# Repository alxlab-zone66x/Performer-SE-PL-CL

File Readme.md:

# Micromac Performer SE/Plus/Classic Clone

This is a recreation of the MicroMac SE/Plus/Classic accelerator.  
The schematics have been reverse engineered and a new PCB was created based on the schematics.

The provided PCB files are licensed under CC-BY-NC-SA - they are NOT intended for commercial use.  

## Notes on GALs and jumpers

The original GALs have been dumped. GAL16V8-15 as well as PALCE16V8-15 have been tested as suitable replacement.
Faster/slower chips as well as ATF16V8 of any speed haven't been tested so far.

U3, U4, U5 and U6 are mandatory. U7 is only needed for operation in Macintosh Plus and Classic.
Close SJ2 if U7 isn't installed. SJ2 HAS to be open when U7 is installed.

Close SJ1 to run the optional 68882 off the 16MHz accelerator clock.
Install an oscillator and open SJ1 to run the 68882 at any speed.
The original design used 25MHz which has been verified to work on the clone as well.

I have not found a socket that allows secure installation over the PLCC CPU in the Macintosh Classic.
Proper operation has been tested in the Macintosh Plus and SE but so far not on the Classic.

## Board Files

The provided gerber files have been generated using the JLCPCB EAGLE cam job files.  

The Kicad project files are placed inside the `kicad` folder. It's been slightly tweaked from the original Eagle project to pass DRC. The silkscreen for the Macintosh Classic and Macintosh Plus were moved to the bottom.

| Board Revision                | Description                                                  |                                                              |
| :---------------------------- | ------------------------------------------------------------ | ------------------------------------------------------------ |
| Performer PL-CL-SE            | Original recreation by Bolle.                                | [gerbers and bom](production/Performer_PL-CL-SE.zip)         |
| Performer SE v1.0 socket pga  | SE only, 2 layers, PGA FPU, PGA CPU, PLCC-20 through-hole sockets | [gerbers and assembly](production/Performer-SE_v1.0_socket-pga.zip) |
| Performer SE v1.1 socket pga  | SE only, 2 layers, PGA FPU, PGA CPU, PLCC-20 through-hole sockets | [gerbers and assembly](production/Performer-SE_v1.1_socket-pga.zip) |
| Performer SE v1.0 socket plcc | SE only, 2 layers, PLCC FPU, PGA CPU, PLCC-20 through-hole sockets | [gerbers and assembly](production/Performer-SE_v1.0_socket-plcc.zip) |
| Performer SE v1.1 socket plcc | SE only, 2 layers, PLCC FPU, PGA CPU, PLCC-20 through-hole sockets | [gerbers and assembly](production/Performer-SE_v1.1_socket-plcc.zip) |

## Bill of Materials

### Performer SE

Parts shared between the Performer SE design variations.

| Quantity | Description                                     | Designators                                                  | Product Number                                               |
| :------- | ----------------------------------------------- | ------------------------------------------------------------ | ------------------------------------------------------------ |
| 4        | 100uF 6.3v 1206 mlcc                            | C1, C2, C3, C4                                               |                                                              |
| 5        | 0.1uF 6.3v 1206 mlcc                            | C5, C6, C7, C8, C9                                           |                                                              |
| 18       | 4.7kOhms 1/4W 1206 resistor                     | R1, R2, R3, R4, R5, R6, R7, R8, R9, R10, R11, R12, R13, R14, R15, R16, R17, R18 |                                                              |
| 4-6      | 0.5mm press-fit pin socket (optional)           | QG1                                                          | [0531-0-15-15-31-27-10-0](docs/datasheets/Mill-Max_0531-0-15-15-31-27-10-0.pdf) |
| 1        | 25MHz oscillator 8-pin or 14-pin dip (optional) | QG1                                                          | [ECS-2200B-250](docs/datasheets/ECS_ECS-2200B-250.pdf), [ECS-100AX-250](docs/datasheets/ECS_ECS-100AX-250.pdf) |
| 1        | pga-128 through-hole socket (optional)          | U1                                                           |                                                              |
| 4        | plcc-20 through-hole socket                     | U3, U4, U5, U6                                               | [PLCC-20-AT](docs/datasheets/Adam-Tech_PLCC-20-AT.pdf)       |

### Performer SE - PLCC FPU

| Quantity | Description                 | Designators | Product Number                                         |
| :------- | --------------------------- | ----------- | ------------------------------------------------------ |
| 1        | plcc-68 through-hole socket | U2          | [PLCC-68-AT](docs/datasheets/Adam-Tech_PLCC-68-AT.pdf) |

### Performer SE - PGA FPU

| Quantity | Description                           | Designators | Product Number |
| :------- | ------------------------------------- | ----------- | -------------- |
| 1        | pga-68 through-hole socket (optional) | U2          |                |

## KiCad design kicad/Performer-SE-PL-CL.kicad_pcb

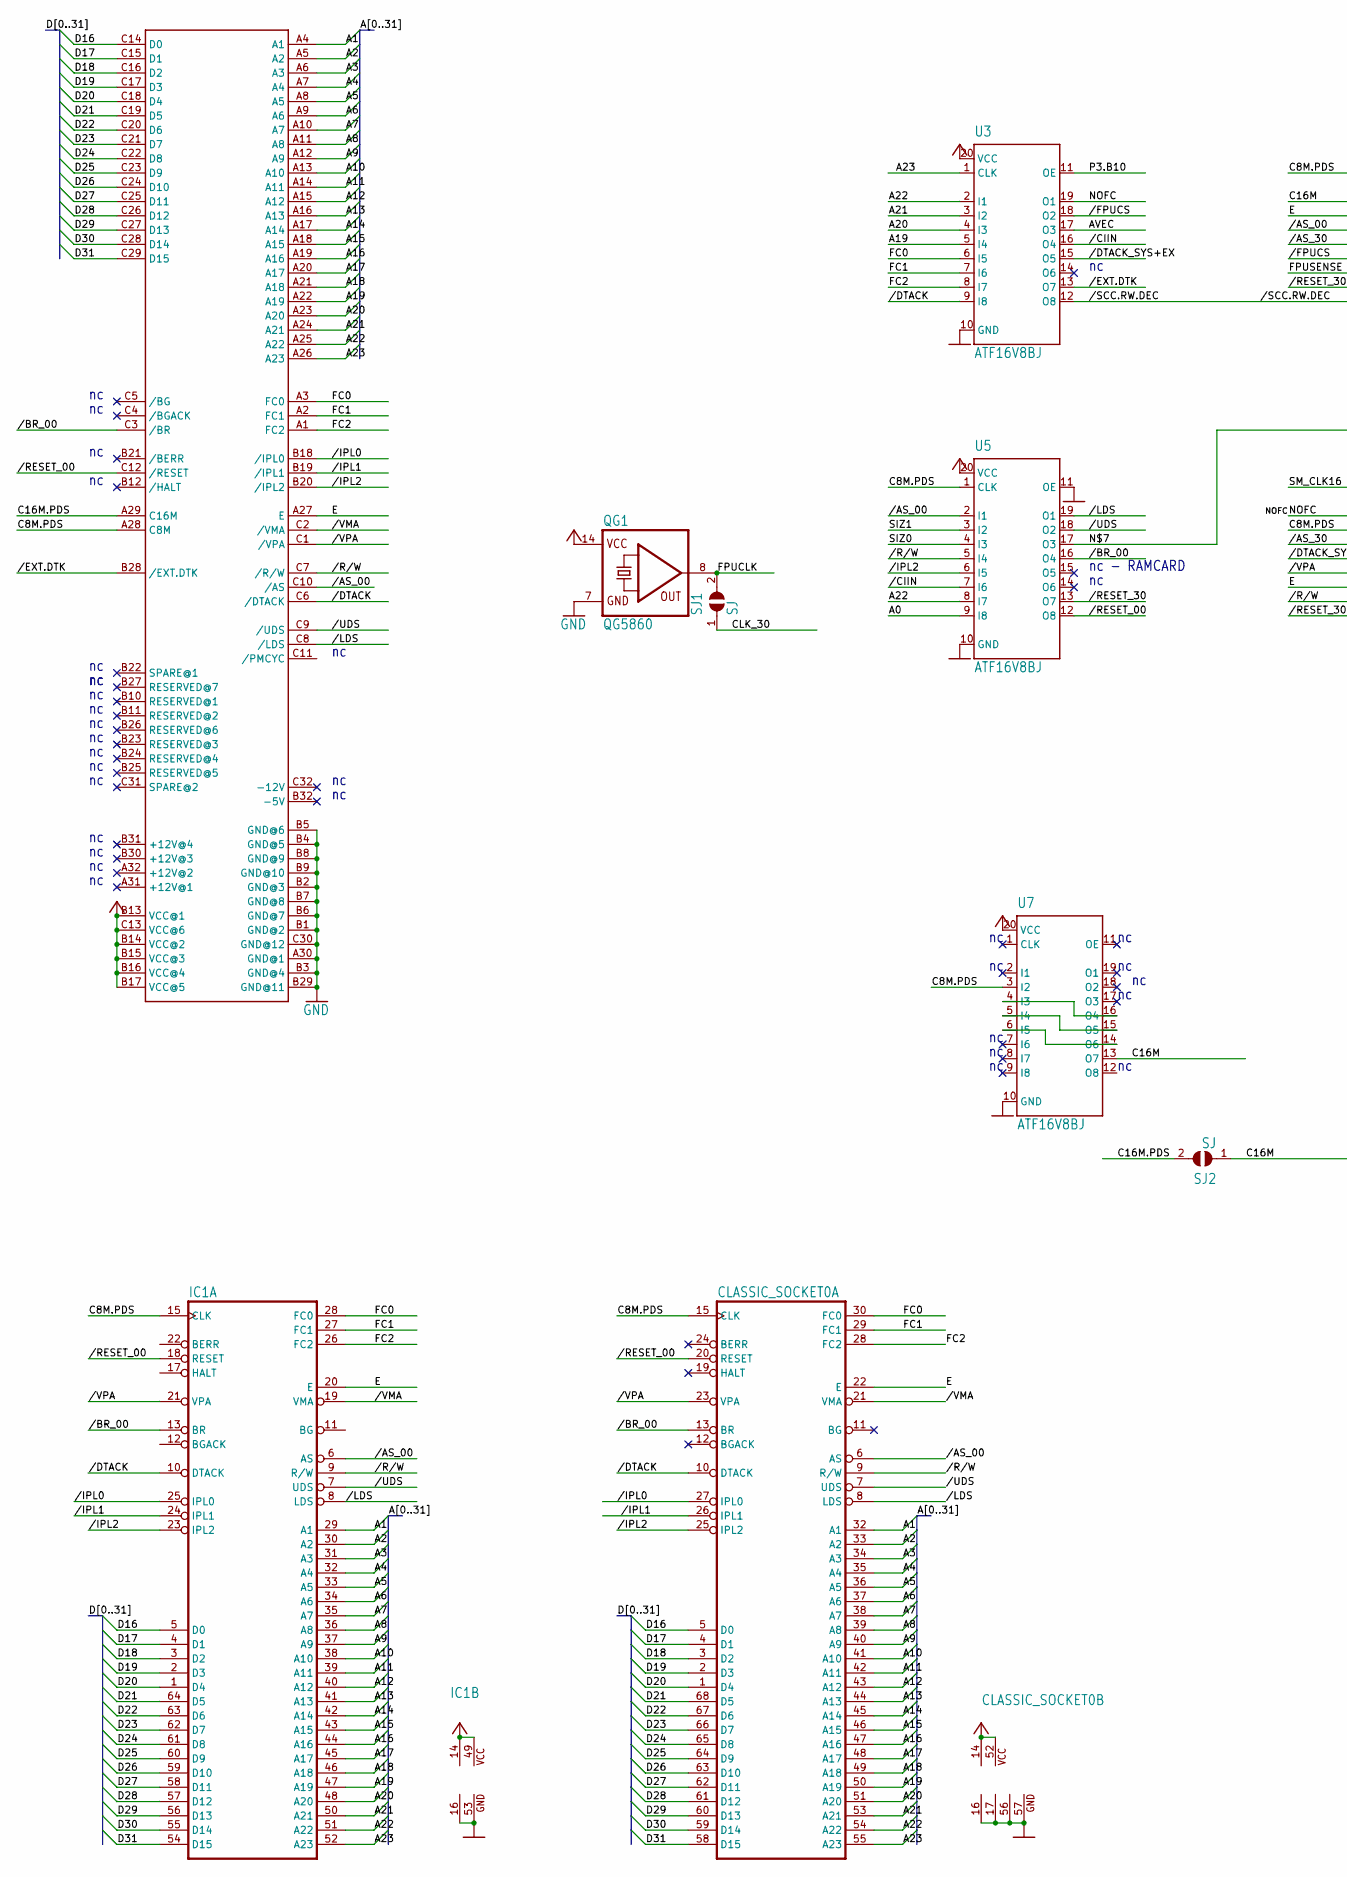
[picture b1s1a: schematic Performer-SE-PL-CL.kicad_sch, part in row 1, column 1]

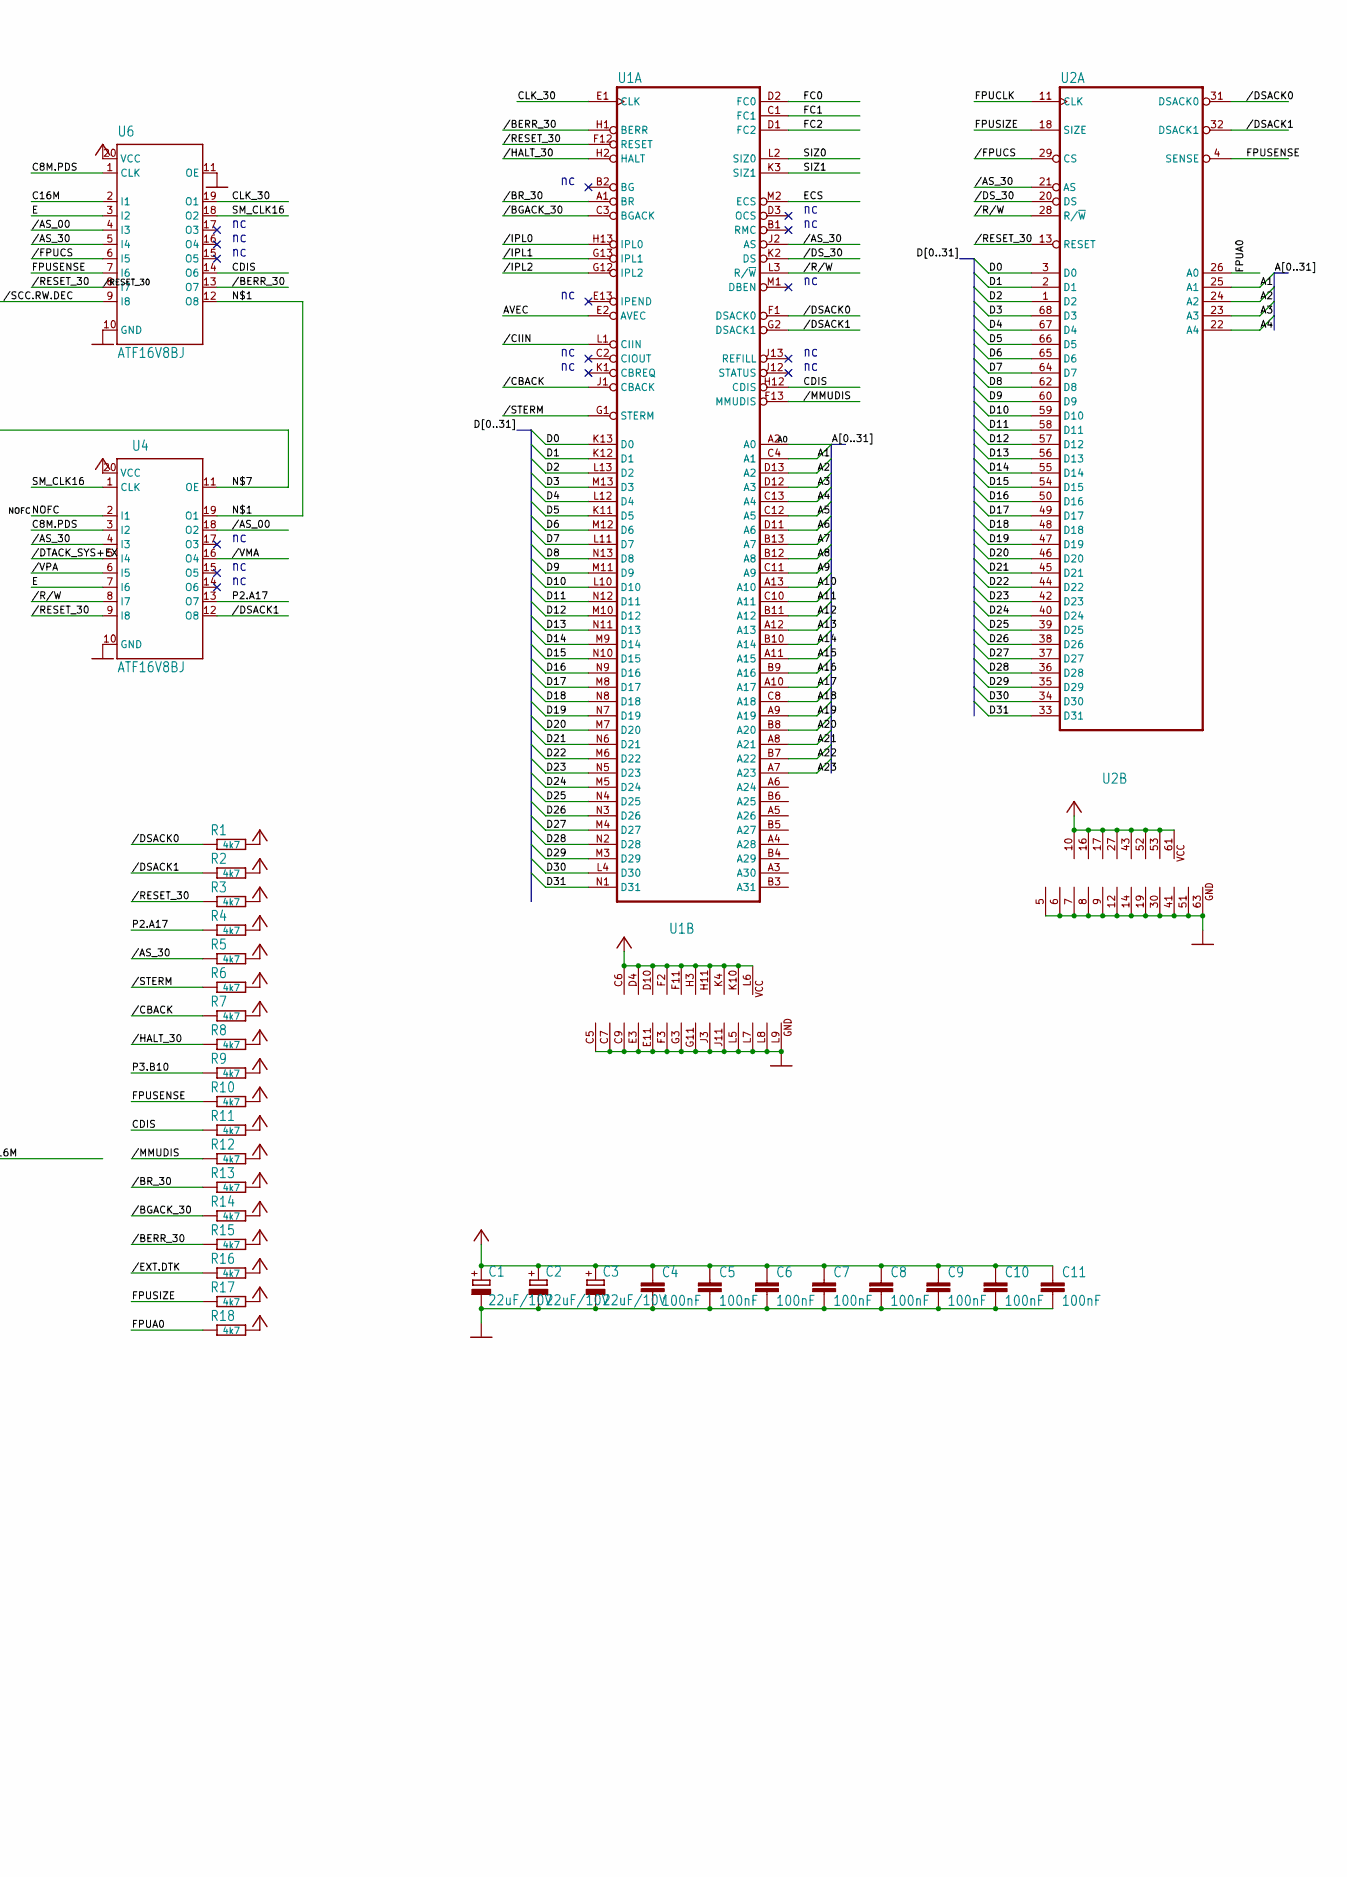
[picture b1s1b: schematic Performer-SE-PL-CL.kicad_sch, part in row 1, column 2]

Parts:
C1, C2, C3: 22uF/10V; CP_EIA-6032-15_Kemet-U_Pad2.25x2.35mm_HandSolder
C4, C5, C6, C7, C8, C9, C10, C11: 100nF; C_1206_3216Metric_Pad1.60x1.80mm_HandSolder
CLASSIC_SOCKET0: MC68000FN-SOC; PLCC-68_THT-Socket_Mirror
IC1: MC68000P; DIP-64_W22.86mm_LongPads_Mirror
J1: MAC_SE_PDS; DIN41612_R_3x32_Male_Vertical_THT_Mirror_NoMountingHoles
QG1: QG5860; Oscillator_DIP-14
R1, R2, R3, R4, R5, R6, R7, R8, R9, R10, R11, R12, R13, R14, R15, R16, R17, R18: 4k7; R_1206_3216Metric_Pad1.60x1.80mm_HandSolder
SJ1, SJ2: SJ; SolderJumper-2_P1.3mm_Open_TrianglePad1.0x1.5mm
U1: MC68030RC; CPGA-128_Layout13x13_MC68030
U2: MC68881FN-SOC; PLCC-68_THT-Socket
U3, U4, U5, U6, U7: ATF16V8BJ; PLCC-20

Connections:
/A0: U1.A2 (A0), U5.9 (I8)
/A1: CLASSIC_SOCKET0.32 (A1), IC1.29 (A1), J1.A4 (A1), U1.C4 (A1), U2.25 (A1)
/A2: CLASSIC_SOCKET0.33 (A2), IC1.30 (A2), J1.A5 (A2), U1.D13 (A2), U2.24 (A2)
/A3: CLASSIC_SOCKET0.34 (A3), IC1.31 (A3), J1.A6 (A3), U1.D12 (A3), U2.23 (A3)
/A4: CLASSIC_SOCKET0.35 (A4), IC1.32 (A4), J1.A7 (A4), U1.C13 (A4), U2.22 (A4)
/A5: CLASSIC_SOCKET0.36 (A5), IC1.33 (A5), J1.A8 (A5), U1.C12 (A5)
/A6: CLASSIC_SOCKET0.37 (A6), IC1.34 (A6), J1.A9 (A6), U1.D11 (A6)
/A7: CLASSIC_SOCKET0.38 (A7), IC1.35 (A7), J1.A10 (A7), U1.B13 (A7)
/A8: CLASSIC_SOCKET0.39 (A8), IC1.36 (A8), J1.A11 (A8), U1.B12 (A8)
/A9: CLASSIC_SOCKET0.40 (A9), IC1.37 (A9), J1.A12 (A9), U1.C11 (A9)
/A10: CLASSIC_SOCKET0.41 (A10), IC1.38 (A10), J1.A13 (A10), U1.A13 (A10)
/A11: CLASSIC_SOCKET0.42 (A11), IC1.39 (A11), J1.A14 (A11), U1.C10 (A11)
/A12: CLASSIC_SOCKET0.43 (A12), IC1.40 (A12), J1.A15 (A12), U1.B11 (A12)
/A13: CLASSIC_SOCKET0.44 (A13), IC1.41 (A13), J1.A16 (A13), U1.A12 (A13)
/A14: CLASSIC_SOCKET0.45 (A14), IC1.42 (A14), J1.A17 (A14), U1.B10 (A14)
/A15: CLASSIC_SOCKET0.46 (A15), IC1.43 (A15), J1.A18 (A15), U1.A11 (A15)
/A16: CLASSIC_SOCKET0.47 (A16), IC1.44 (A16), J1.A19 (A16), U1.B9 (A16)
/A17: CLASSIC_SOCKET0.48 (A17), IC1.45 (A17), J1.A20 (A17), U1.A10 (A17)
/A18: CLASSIC_SOCKET0.49 (A18), IC1.46 (A18), J1.A21 (A18), U1.C8 (A18)
/A19: CLASSIC_SOCKET0.50 (A19), IC1.47 (A19), J1.A22 (A19), U1.A9 (A19), U3.5 (I4)
/A20: CLASSIC_SOCKET0.51 (A20), IC1.48 (A20), J1.A23 (A20), U1.B8 (A20), U3.4 (I3)
/A21: CLASSIC_SOCKET0.53 (A21), IC1.50 (A21), J1.A24 (A21), U1.A8 (A21), U3.3 (I2)
/A22: CLASSIC_SOCKET0.54 (A22), IC1.51 (A22), J1.A25 (A22), U1.B7 (A22), U3.2 (I1), U5.8 (I7)
/A23: CLASSIC_SOCKET0.55 (A23), IC1.52 (A23), J1.A26 (A23), U1.A7 (A23), U3.1 (CLK)
/AVEC: U1.E2 (AVEC), U3.17 (O3)
/C8M.PDS: CLASSIC_SOCKET0.15 (CLK), IC1.15 (CLK), J1.A28 (C8M), U4.3 (I2), U5.1 (CLK), U6.1 (CLK), U7.3 (I2)
/C16M: SJ2.1, U6.2 (I1), U7.13 (O7)
/C16M.PDS: J1.A29 (C16M), SJ2.2
/CDIS: R11.1, U1.H12 (CDIS), U6.14 (O6)
/CLK_30: SJ1.1, U1.E1 (CLK), U6.19 (O1)
/D0: U1.K13 (D0), U2.3 (D0)
/D1: U1.K12 (D1), U2.2 (D1)
/D2: U1.L13 (D2), U2.1 (D2)
/D3: U1.M13 (D3), U2.68 (D3)
/D4: U1.L12 (D4), U2.67 (D4)
/D5: U1.K11 (D5), U2.66 (D5)
/D6: U1.M12 (D6), U2.65 (D6)
/D7: U1.L11 (D7), U2.64 (D7)
/D8: U1.N13 (D8), U2.62 (D8)
/D9: U1.M11 (D9), U2.60 (D9)
/D10: U1.L10 (D10), U2.59 (D10)
/D11: U1.N12 (D11), U2.58 (D11)
/D12: U1.M10 (D12), U2.57 (D12)
/D13: U1.N11 (D13), U2.56 (D13)
/D14: U1.M9 (D14), U2.55 (D14)
/D15: U1.N10 (D15), U2.54 (D15)
/D16: CLASSIC_SOCKET0.5 (D0), IC1.5 (D0), J1.C14 (D0), U1.N9 (D16), U2.50 (D16)
/D17: CLASSIC_SOCKET0.4 (D1), IC1.4 (D1), J1.C15 (D1), U1.M8 (D17), U2.49 (D17)
/D18: CLASSIC_SOCKET0.3 (D2), IC1.3 (D2), J1.C16 (D2), U1.N8 (D18), U2.48 (D18)
/D19: CLASSIC_SOCKET0.2 (D3), IC1.2 (D3), J1.C17 (D3), U1.N7 (D19), U2.47 (D19)
/D20: CLASSIC_SOCKET0.1 (D4), IC1.1 (D4), J1.C18 (D4), U1.M7 (D20), U2.46 (D20)
/D21: CLASSIC_SOCKET0.68 (D5), IC1.64 (D5), J1.C19 (D5), U1.N6 (D21), U2.45 (D21)
/D22: CLASSIC_SOCKET0.67 (D6), IC1.63 (D6), J1.C20 (D6), U1.M6 (D22), U2.44 (D22)
/D23: CLASSIC_SOCKET0.66 (D7), IC1.62 (D7), J1.C21 (D7), U1.N5 (D23), U2.42 (D23)
/D24: CLASSIC_SOCKET0.65 (D8), IC1.61 (D8), J1.C22 (D8), U1.M5 (D24), U2.40 (D24)
/D25: CLASSIC_SOCKET0.64 (D9), IC1.60 (D9), J1.C23 (D9), U1.N4 (D25), U2.39 (D25)
/D26: CLASSIC_SOCKET0.63 (D10), IC1.59 (D10), J1.C24 (D10), U1.N3 (D26), U2.38 (D26)
/D27: CLASSIC_SOCKET0.62 (D11), IC1.58 (D11), J1.C25 (D11), U1.M4 (D27), U2.37 (D27)
/D28: CLASSIC_SOCKET0.61 (D12), IC1.57 (D12), J1.C26 (D12), U1.N2 (D28), U2.36 (D28)
/D29: CLASSIC_SOCKET0.60 (D13), IC1.56 (D13), J1.C27 (D13), U1.M3 (D29), U2.35 (D29)
/D30: CLASSIC_SOCKET0.59 (D14), IC1.55 (D14), J1.C28 (D14), U1.L4 (D30), U2.34 (D30)
/D31: CLASSIC_SOCKET0.58 (D15), IC1.54 (D15), J1.C29 (D15), U1.N1 (D31), U2.33 (D31)
/E: CLASSIC_SOCKET0.22 (E), IC1.20 (E), J1.A27 (E), U4.7 (I6), U6.3 (I2)
/ECS: U1.M2 (ECS)
/FC0: CLASSIC_SOCKET0.30 (FC0), IC1.28 (FC0), J1.A3 (FC0), U1.D2 (FC0), U3.6 (I5)
/FC1: CLASSIC_SOCKET0.29 (FC1), IC1.27 (FC1), J1.A2 (FC1), U1.C1 (FC1), U3.7 (I6)
/FC2: CLASSIC_SOCKET0.28 (FC2), IC1.26 (FC2), J1.A1 (FC2), U1.D1 (FC2), U3.8 (I7)
/FPUA0: R18.1, U2.26 (A0)
/FPUCLK: QG1.8 (OUT), SJ1.2, U2.11 (CLK)
/FPUSENSE: R10.1, U2.4 (SENSE), U6.7 (I6)
/FPUSIZE: R17.1, U2.18 (SIZE)
/N$1: U4.19 (O1), U6.12 (O8)
/N$7: U4.11 (OE), U5.17 (O3)
/NOFC: U3.19 (O1), U4.2 (I1)
/P2.A17: R4.1, U4.13 (O7)
/P3.B10: R9.1, U3.11 (OE)
/SIZ0: U1.L2 (SIZ0), U5.4 (I3)
/SIZ1: U1.K3 (SIZ1), U5.3 (I2)
/SM_CLK16: U4.1 (CLK), U6.18 (O2)
//AS_00: CLASSIC_SOCKET0.6 (AS), IC1.6 (AS), J1.C10 (/AS), U4.18 (O2), U5.2 (I1), U6.4 (I3)
//AS_30: R5.1, U1.J2 (AS), U2.21 (AS), U4.4 (I3), U6.5 (I4)
//BERR_30: R15.1, U1.H1 (BERR), U6.13 (O7)
//BGACK_30: R14.1, U1.C3 (BGACK)
//BR_00: CLASSIC_SOCKET0.13 (BR), IC1.13 (BR), J1.C3 (/BR), U5.16 (O4)
//BR_30: R13.1, U1.A1 (BR)
//CBACK: R7.1, U1.J1 (CBACK)
//CIIN: U1.L1 (CIIN), U3.16 (O4), U5.7 (I6)
//DSACK0: R1.1, U1.F1 (DSACK0), U2.31 (DSACK0)
//DSACK1: R2.1, U1.G2 (DSACK1), U2.32 (DSACK1), U4.12 (O8)
//DS_30: U1.K2 (DS), U2.20 (DS)
//DTACK: CLASSIC_SOCKET0.10 (DTACK), IC1.10 (DTACK), J1.C6 (/DTACK), U3.9 (I8)
//DTACK_SYS+EX: U3.15 (O5), U4.5 (I4)
//EXT.DTK: J1.B28 (/EXT.DTK), R16.1, U3.13 (O7)
//FPUCS: U2.29 (CS), U3.18 (O2), U6.6 (I5)
//HALT_30: R8.1, U1.H2 (HALT)
//IPL0: CLASSIC_SOCKET0.27 (IPL0), IC1.25 (IPL0), J1.B18 (/IPL0), U1.H13 (IPL0)
//IPL1: CLASSIC_SOCKET0.26 (IPL1), IC1.24 (IPL1), J1.B19 (/IPL1), U1.G13 (IPL1)
//IPL2: CLASSIC_SOCKET0.25 (IPL2), IC1.23 (IPL2), J1.B20 (/IPL2), U1.G12 (IPL2), U5.6 (I5)
//LDS: CLASSIC_SOCKET0.8 (LDS), IC1.8 (LDS), J1.C8 (/LDS), U5.19 (O1)
//MMUDIS: R12.1, U1.F13 (MMUDIS)
//RESET_00: CLASSIC_SOCKET0.20 (RESET), IC1.18 (RESET), J1.C12 (/RESET), U5.12 (O8)
//RESET_30: R3.1, U1.F12 (RESET), U2.13 (RESET), U4.9 (I8), U5.13 (O7), U6.8 (I7)
//R/W: CLASSIC_SOCKET0.9 (R/W), IC1.9 (R/W), J1.C7 (/R/W), U1.L3 (R/~W), U2.28 (R/~W), U4.8 (I7), U5.5 (I4)
//SCC.RW.DEC: U3.12 (O8), U6.9 (I8)
//STERM: R6.1, U1.G1 (STERM)
//UDS: CLASSIC_SOCKET0.7 (UDS), IC1.7 (UDS), J1.C9 (/UDS), U5.18 (O2)
//VMA: CLASSIC_SOCKET0.21 (VMA), IC1.19 (VMA), J1.C2 (/VMA), U4.16 (O4)
//VPA: CLASSIC_SOCKET0.23 (VPA), IC1.21 (VPA), J1.C1 (/VPA), U4.6 (I5)
GND: C1.-, C2.-, C3.-, C4.2, C5.2, C6.2, C7.2, C8.2, C9.2, C10.2, C11.2, CLASSIC_SOCKET0.16 (GND@1), CLASSIC_SOCKET0.17 (GND@2), CLASSIC_SOCKET0.56 (GND@3), CLASSIC_SOCKET0.57 (GND@4), IC1.16 (GND@1), IC1.53 (GND@2), J1.A30 (GND@1), J1.B1 (GND@2), J1.B2 (GND@3), J1.B3 (GND@4), J1.B4 (GND@5), J1.B5 (GND@6), J1.B6 (GND@7), J1.B7 (GND@8), J1.B8 (GND@9), J1.B9 (GND@10), J1.B29 (GND@11), J1.C30 (GND@12), QG1.7 (GND), U1.C5 (GND@1), U1.C7 (GND@2), U1.C9 (GND@3), U1.E3 (GND@4), U1.E11 (GND@5), U1.F3 (GND@6), U1.G3 (GND@7), U1.G11 (GND@8), U1.J3 (GND@9), U1.J11 (GND@10), U1.L5 (GND@11), U1.L7 (GND@12), U1.L8 (GND@13), U1.L9 (GND@14), U2.5 (GND@1), U2.6 (GND@2), U2.7 (GND@3), U2.8 (GND@4), U2.9 (GND@5), U2.12 (GND@6), U2.14 (GND@7), U2.19 (GND@8), U2.30 (GND@9), U2.41 (GND@10), U2.51 (GND@11), U2.63 (GND@12), U3.10 (GND), U4.10 (GND), U5.10 (GND), U5.11 (OE), U6.10 (GND), U6.11 (OE), U7.10 (GND)
unnamed: U7.4 (I3), U7.16 (O4)
unnamed: U7.5 (I4), U7.15 (O5)
unnamed: U7.6 (I5), U7.14 (O6)
VCC: C1.+, C2.+, C3.+, C4.1, C5.1, C6.1, C7.1, C8.1, C9.1, C10.1, C11.1, CLASSIC_SOCKET0.14 (VCC@1), CLASSIC_SOCKET0.52 (VCC@2), IC1.14 (VCC@1), IC1.49 (VCC@2), J1.B13 (VCC@1), J1.B14 (VCC@2), J1.B15 (VCC@3), J1.B16 (VCC@4), J1.B17 (VCC@5), J1.C13 (VCC@6), QG1.14 (VCC), R1.2, R2.2, R3.2, R4.2, R5.2, R6.2, R7.2, R8.2, R9.2, R10.2, R11.2, R12.2, R13.2, R14.2, R15.2, R16.2, R17.2, R18.2, U1.C6 (VCC@1), U1.D4 (VCC@2), U1.D10 (VCC@3), U1.F2 (VCC@4), U1.F11 (VCC@5), U1.H3 (VCC@6), U1.H11 (VCC@7), U1.K4 (VCC@8), U1.K10 (VCC@9), U1.L6 (VCC@10), U2.10 (VCC@1), U2.16 (VCC@2), U2.17 (VCC@3), U2.27 (VCC@4), U2.43 (VCC@5), U2.52 (VCC@6), U2.53 (VCC@7), U2.61 (VCC@8), U3.20 (VCC), U4.20 (VCC), U5.20 (VCC), U6.20 (VCC), U7.20 (VCC)

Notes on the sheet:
nc - RAMCARD

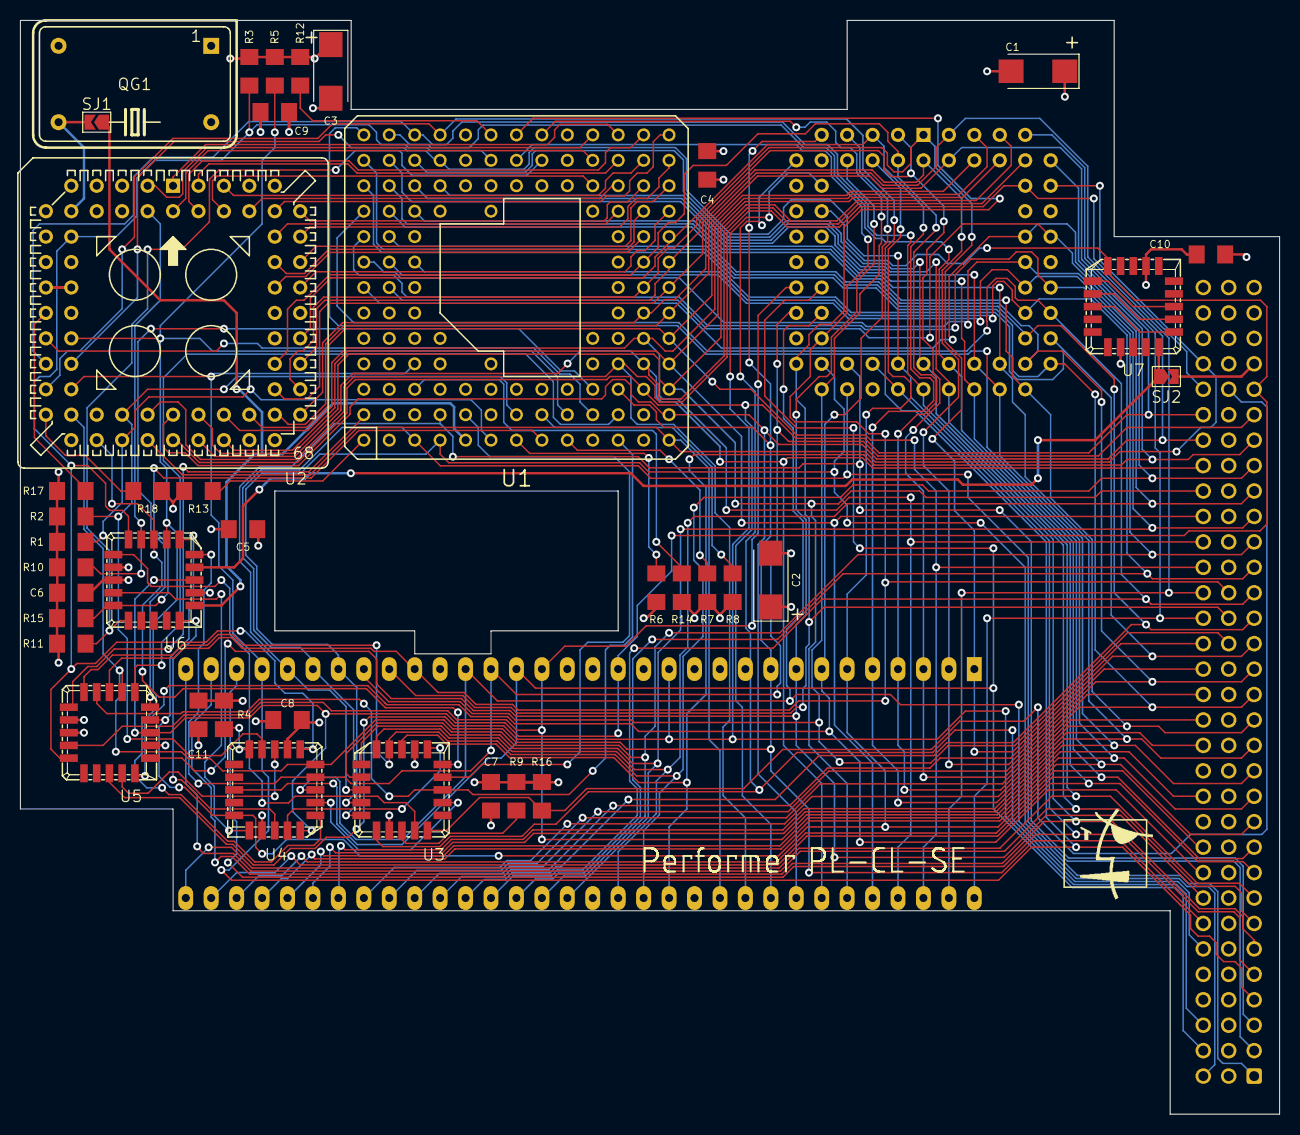
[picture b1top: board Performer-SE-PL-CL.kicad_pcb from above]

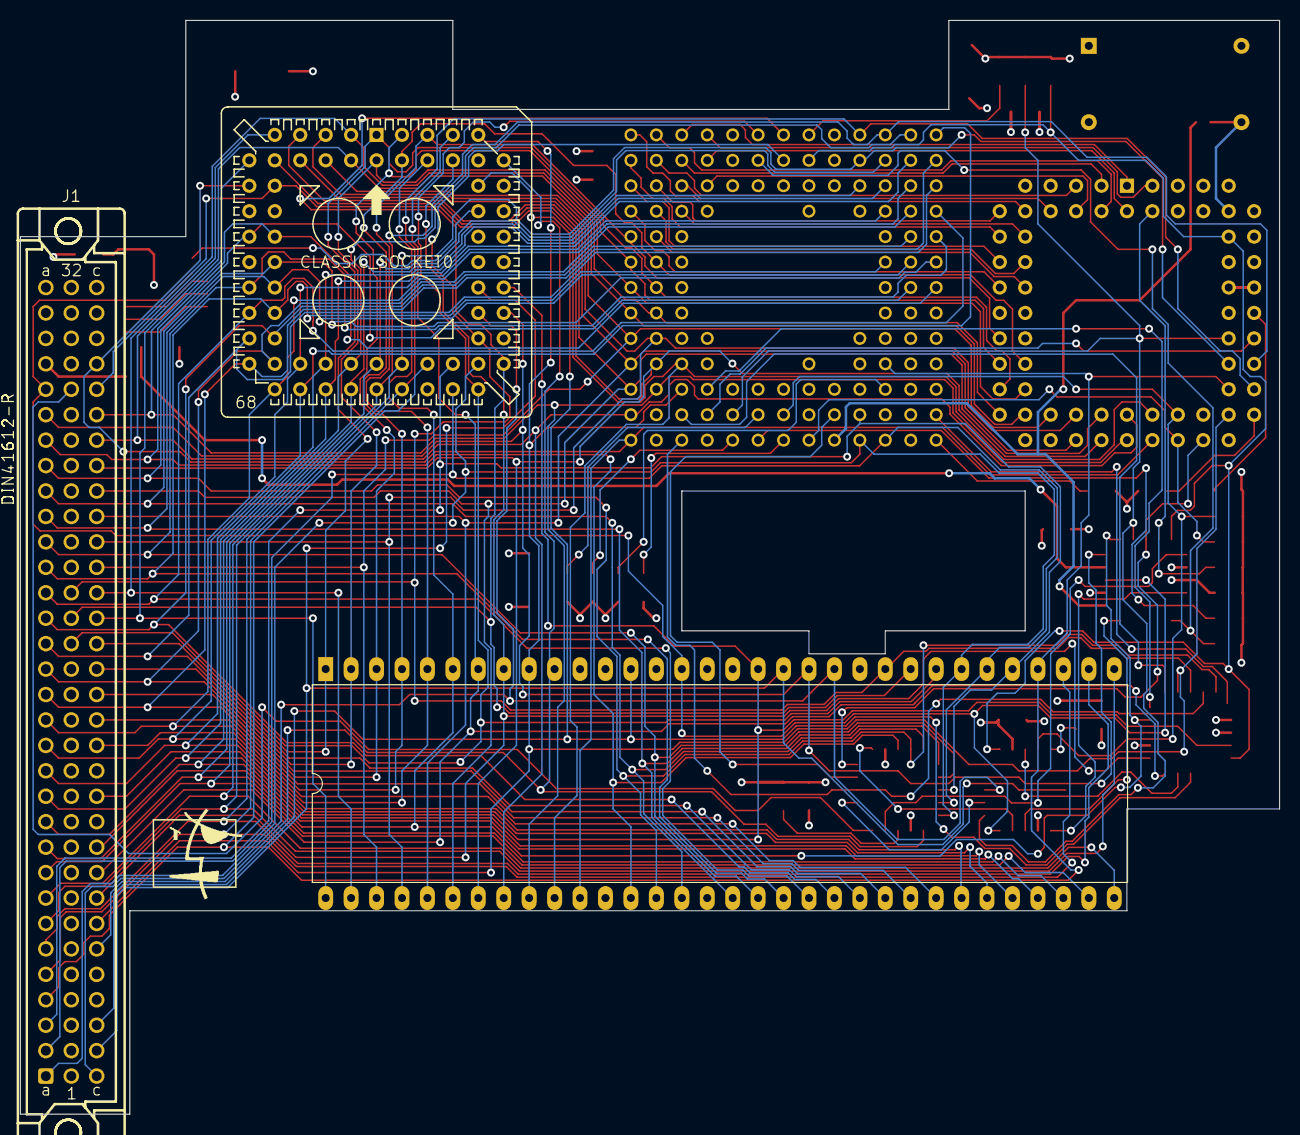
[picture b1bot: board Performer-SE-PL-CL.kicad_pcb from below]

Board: 4 copper layers, 125.7 x 109.2 mm, 42 parts (3 on the bottom side), 112 nets.

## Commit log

2024-10-14 Add Kicad project files
2024-10-14 Rename MC68030 Kicad footprint
2024-10-14 Update the MC68030 footprint
2024-10-27 Update and add footprints/symbols
2024-10-27 Update PDS footprint of the Performer-SE-PL-CL
2024-10-27 Remove extra silkscreens from Performer-SE-PL-CL
2024-11-24 Add Performer SE revision
2025-01-26 Add missing C9 in readme
